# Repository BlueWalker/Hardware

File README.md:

Hardware
===

Schematic
---

Case
---

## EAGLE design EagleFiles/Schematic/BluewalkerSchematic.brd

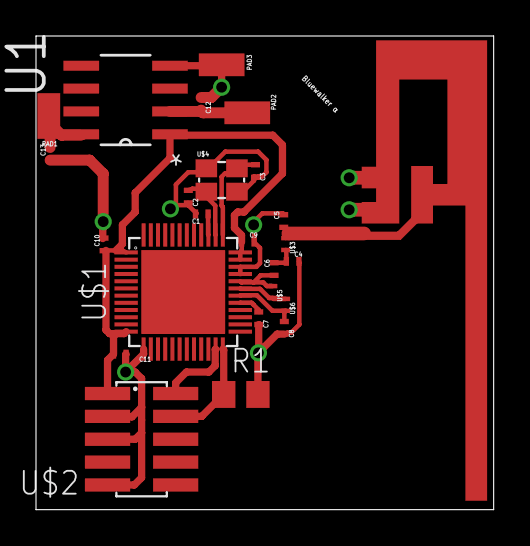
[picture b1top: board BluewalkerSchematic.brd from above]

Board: 2 copper layers, 25.4 x 26.3 mm, 24 parts (0 on the bottom side), 17 nets.

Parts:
C1, C10, C11: 100nF; 0402CAPACITOR
C2, C3: 12pF; 0402CAPACITOR
C4: 1pF; 0402CAPACITOR
C5: 1.5pF; 0402CAPACITOR
C6: 2.2pF; 0402CAPACITOR
C7: 47nF; 0402CAPACITOR
C8: 2.2nF; 0402CAPACITOR
C9: 1nF; 0402CAPACITOR
C12, C13: .047uF; 0402CAPACITOR
PAD1, PAD2, PAD3: SMD1,27-2,54
R1: 12 k; R0805
U1: ICL7673CBAZA; SOIC127P600X175-8N
U$1: NRF51822; QFN48
U$2: PIN_HEADER_IO; M50-3600742
U$3: 3.3 nH; 0402INDUCTOR
U$4: CRYSTAL2.5X2; 2.5X2MM
U$5: 4.7 nH; 0402INDUCTOR
U$6: 10 nH; 0402INDUCTOR

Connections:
GROUND: C1.1, C2.1, C3.1, C4.1, C5.1, C7.1, C8.1, C9.1, C11.1, PAD3.1, R1.2, U1.4, U$1.13, U$1.33, U$1.34, U$2.3, U$2.5, U$2.9, U$4.GND, U$4.GND2
unnamed: C1.2, U$1.39
unnamed: C2.2, U$1.38, U$4.X2
unnamed: C3.2, U$1.37, U$4.X1
unnamed: C7.2, U$1.29
unnamed: C12.2, U1.2
unnamed: C13.2, U1.8
unnamed: C6.2, U$1.32, U$5.2
unnamed: U$1.23, U$2.2
unnamed: R1.1, U$1.24, U$2.4
unnamed: C8.2, U$1.30, U$6.1
unnamed: U$1.31, U$5.1, U$6.2
unnamed: C13.1, PAD1.1
unnamed: C12.1, PAD2.1
unnamed: C4.2, C6.1, U$3.1
unnamed: C5.2, U$3.2
VCC: C9.2, C10.2, C11.2, U1.1, U$1.1, U$1.12, U$1.35, U$1.36, U$2.1

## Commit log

2015-04-30 Added schematic files
2015-04-30 Added images and README
